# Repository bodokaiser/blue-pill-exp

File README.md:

# Blue Pill Exp

Experiments with the Blue Pill.

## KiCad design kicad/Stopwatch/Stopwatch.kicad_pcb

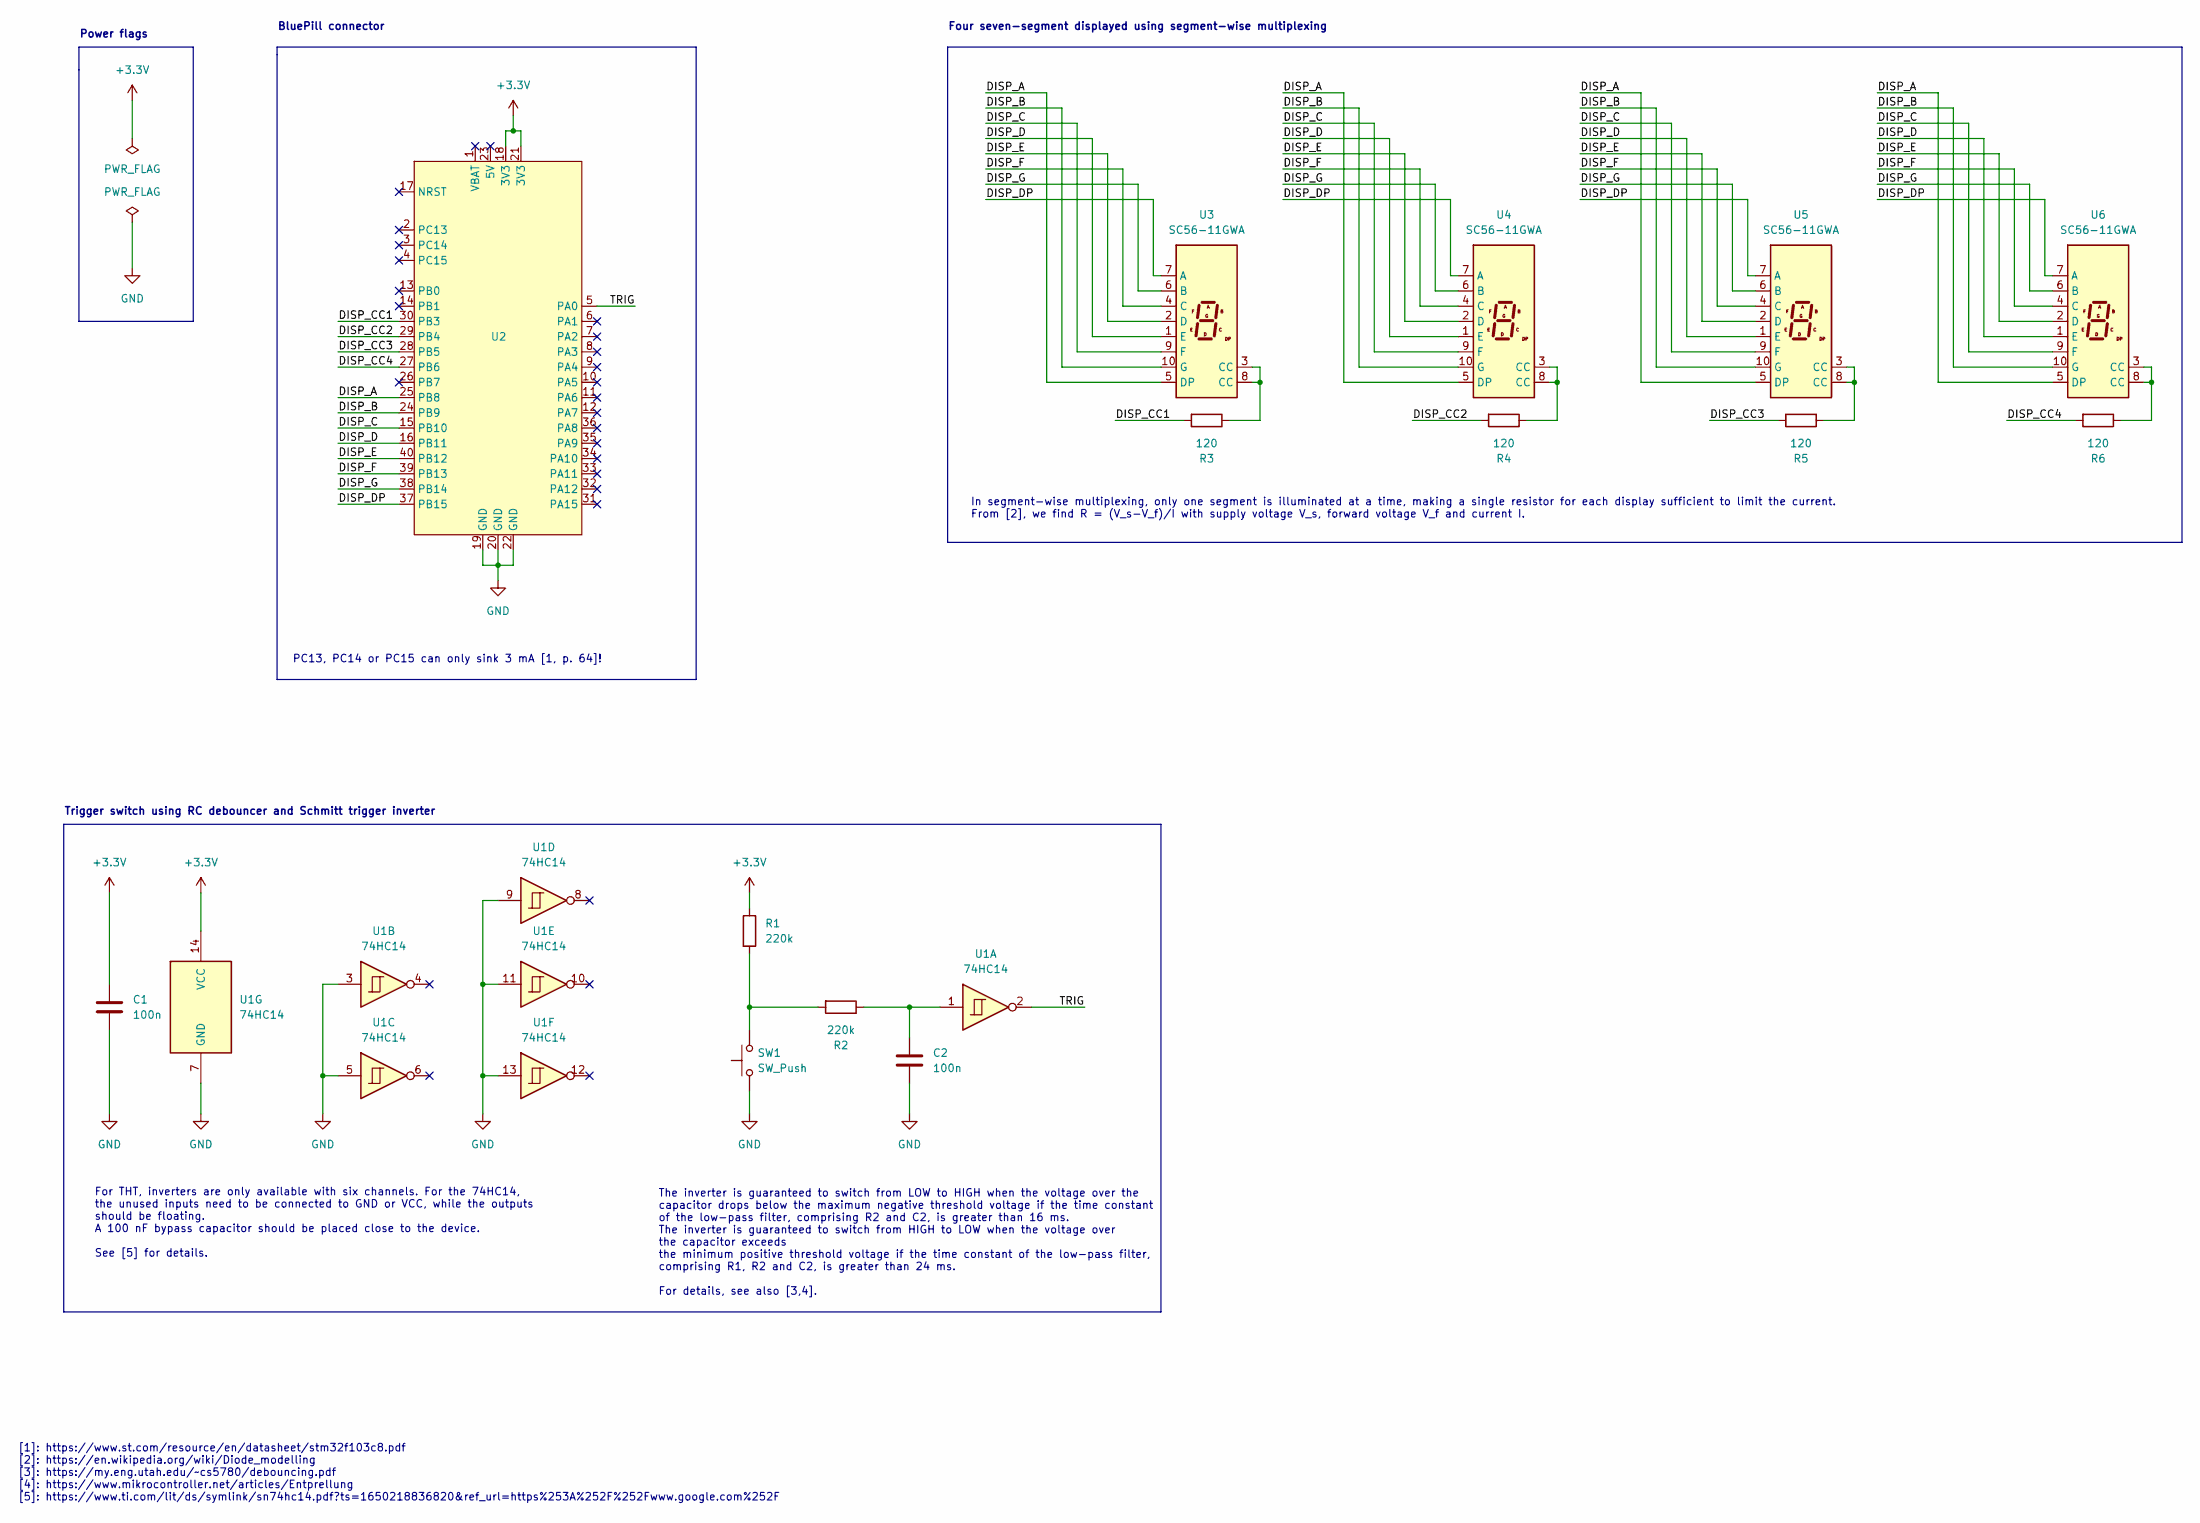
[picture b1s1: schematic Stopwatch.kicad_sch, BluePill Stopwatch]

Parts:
C1, C2: 100n; C_Disc_D3.0mm_W2.0mm_P2.50mm
R1, R2: 220k; R_Axial_DIN0207_L6.3mm_D2.5mm_P10.16mm_Horizontal
R3, R4, R5, R6: 120; R_Axial_DIN0207_L6.3mm_D2.5mm_P10.16mm_Horizontal
SW1: SW_Push; 5ETH935
U1: 74HC14; DIP-14_W7.62mm
U2: (no value)
U3, U4, U5, U6: SC56-11GWA

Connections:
+3V3: C1.1, R1.1, U1.14 (VCC), U2.18 (3V3), U2.21 (3V3)
/DISP_A: U2.25 (PB8), U3.5 (DP), U4.5 (DP), U5.5 (DP), U6.5 (DP)
/DISP_B: U2.24 (PB9), U3.10 (G), U4.10 (G), U5.10 (G), U6.10 (G)
/DISP_C: U2.15 (PB10), U3.9 (F), U4.9 (F), U5.9 (F), U6.9 (F)
/DISP_CC1: R3.2, U2.30 (PB3)
/DISP_CC2: R4.2, U2.29 (PB4)
/DISP_CC3: R5.2, U2.28 (PB5)
/DISP_CC4: R6.2, U2.27 (PB6)
/DISP_D: U2.16 (PB11), U3.1 (E), U4.1 (E), U5.1 (E), U6.1 (E)
/DISP_DP: U2.37 (PB15), U3.7 (A), U4.7 (A), U5.7 (A), U6.7 (A)
/DISP_E: U2.40 (PB12), U3.2 (D), U4.2 (D), U5.2 (D), U6.2 (D)
/DISP_F: U2.39 (PB13), U3.4 (C), U4.4 (C), U5.4 (C), U6.4 (C)
/DISP_G: U2.38 (PB14), U3.6 (B), U4.6 (B), U5.6 (B), U6.6 (B)
/TRIG: U1.2, U2.5 (PA0)
GND: C1.2, C2.2, SW1.1, U1.3, U1.5, U1.7 (GND), U1.9, U1.11, U1.13, U2.19 (GND), U2.20 (GND), U2.22 (GND)
unnamed: C2.1, R2.1, U1.1
unnamed: R1.2, R2.2, SW1.2
unnamed: R3.1, U3.3 (CC), U3.8 (CC)
unnamed: R4.1, U4.3 (CC), U4.8 (CC)
unnamed: R5.1, U5.3 (CC), U5.8 (CC)
unnamed: R6.1, U6.3 (CC), U6.8 (CC)

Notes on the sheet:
For THT, inverters are only available with six channels. For the 74HC14, the unused inputs need to be connected to GND or VCC, while the outputs should be floating. A 100 nF bypass capacitor should be placed close to the device. See [5] for details.
Power flags
[1]: https://www.st.com/resource/en/datasheet/stm32f103c8.pdf [2]: https://en.wikipedia.org/wiki/Diode_modelling [3]: https://my.eng.utah.edu/~cs5780/debouncing.pdf [4]: https://www.mikrocontroller.net/articles/Entprellung [5]: https://www.ti.com/lit/ds/symlink/sn74hc14.pdf?ts=1650218836820&ref_url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
BluePill connector
In segment-wise multiplexing, only one segment is illuminated at a time, making a single resistor for each display sufficient to limit the current. From [2], we find R = (V_s-V_f)/I with supply voltage V_s, forward voltage V_f and current I.
Trigger switch using RC debouncer and Schmitt trigger inverter
PC13, PC14 or PC15 can only sink 3 mA [1, p. 64]!
The inverter is guaranteed to switch from LOW to HIGH when the voltage over the capacitor drops below the maximum negative threshold voltage if the time constant of the low-pass filter, comprising R2 and C2, is greater than 16 ms. The inverter is guaranteed to switch from HIGH to LOW when the volta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
Four seven-segment displayed using segment-wise multiplexing

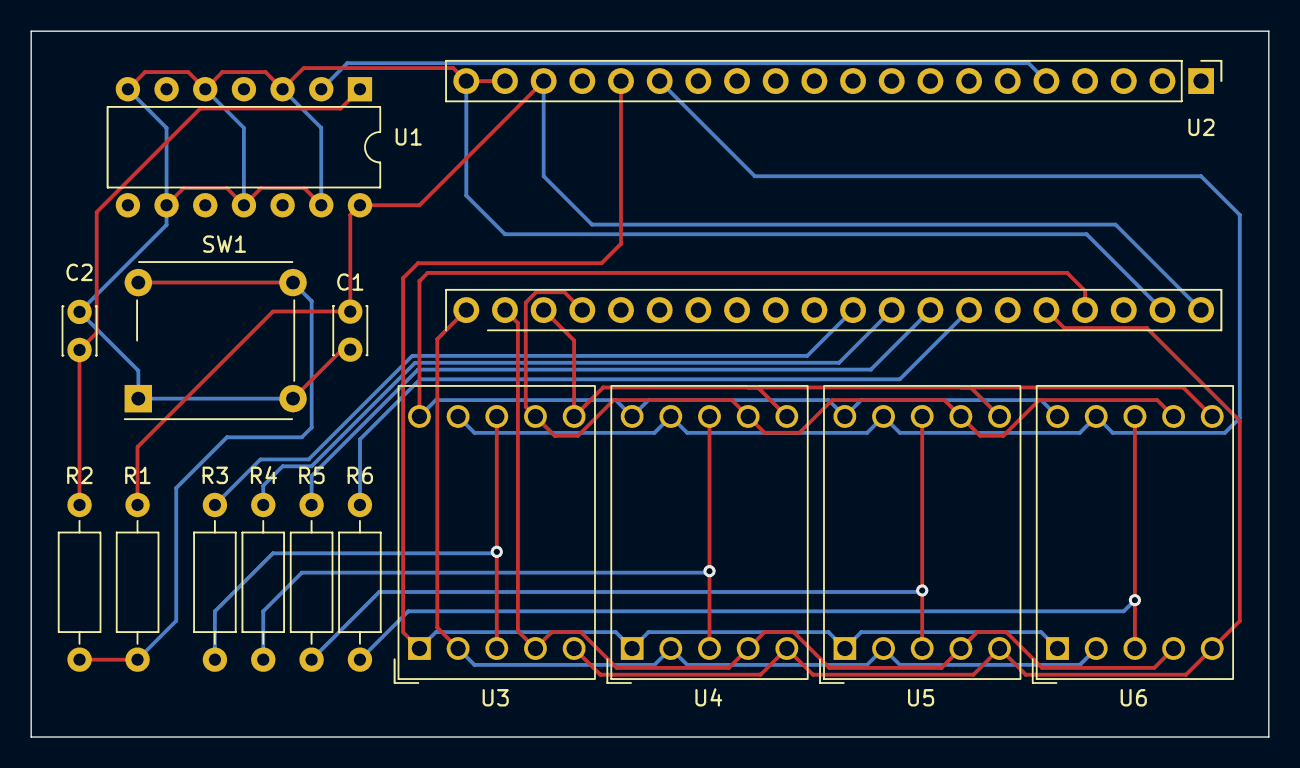
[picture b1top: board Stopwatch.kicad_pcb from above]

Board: 2 copper layers, 81.3 x 46.4 mm, 15 parts (0 on the bottom side), 21 nets.

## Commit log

2022-04-10 started Stopwatch KiCad schematic
2022-04-10 added BluePill to symbol library, completed first draft of Stopwatch schematic
2022-04-15 updated Stopwatch with calculation for debouncer circuit
2022-04-16 fixed custom BluePill symbol and updated Stopwatch schematic
2022-04-18 added custom footprint library with SC56-11GWA, assigned available footprints
2022-04-18 fixed BluePill symbol pin numbers, added button and BluePill footprint
2022-05-02 completed pcb design of stopwatch
